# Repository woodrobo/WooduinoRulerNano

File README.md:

# WooduinoRulerNano
WooduinoRulerNanoは定規風Arduino Nano互換機です。  
定規っぽい見た目なだけでなく、電源電流マシマシに設計していて、3.3Vには800mAの3端子レギュレータを採用していて5Vも配線幅的には2Aほど流せます。Vin端子は使ったこと無かったのでつけていないです。  
[BOOTH](https://woodrobo.booth.pm/items/3751720)で販売しています。

# 部品・はんだづけについて
add_info/部品表.csvを見てはんだづけを行ってください。  
(ちなみにCH340GではなくCH340Cを使用すればC3,C4,Y1を省略できます)  
向きを間違えやすい4つの箇所を説明します。  

1.クリスタル(12MHz)  
赤枠が1番ピンなので赤枠同士が合うようにしてください。裏面の方が分かりやすいので裏面も写真にのせています。  

2.CH340G  
〇のマークは1番ピンの意味なので、〇のマークに注目して画像と同様の向きにしてください。  

3.ATMEGA328P  
〇のマークは1番ピンの意味なので、〇のマークに注目して画像と同様の向きにしてください。  

4.LED  
LEDにはアノード・カソードという端子があり極性があります。写真のような向きにしてください。裏面の方が分かりやすいので裏面も写真にのせています。  

# ブートローダ書き込みについて
Arduinoはブートローダと呼ばれるプログラムを書きこむためのプログラムを書きこむことで動作します。公式の説明は[ここ](https://docs.arduino.cc/built-in-examples/arduino-isp/ArduinoISP)。  
ここではArduino Unoを用いてWooduinoRulerNanoに書きこみを行う方法を説明します。(WooduinoRulerNanoはArduino Nano互換機なのでArduino Nanoについて解説されている他のサイトも参考にしてみてください)  

※Arduino Unoの代わりにArduino Nanoを用いてもやり方は同じです。Arduino UnoのところをArduino Nanoに読み替えてください。 それ以外のArduinoから書き込みを行いたい場合は他のサイトを参照してください。 

**テスト環境**  
ArduinoIDE 1.8.13  
Windows 10

**1.まずはArduino Unoにブートローダ書き込み用のプログラムを書きこみます。**

ファイル->スケッチ例->ArduinoISP->ArduinoISPを開きます。  
Arduino Unoに書きこみます。  

**2.Arduino UnoとWooduinoRulerNanoを結線します。**

書き込みには以下の表に示すように6本の配線が必要です。配線時にはどちらも電源供給は行わないでください。RESETの機能に関しては書き込み機と書き込み対象でピンが違うので注意してください。

|  機能  |  書き込み機(Arduino Uno)  |  WooduinoRulerNano
| ---- | ---- |  ----  |
|  MOSI  |  11  |  11  |
|  MISO  |  12  |  12  |
|  SCK  |  13  |  13  |
|  RESET  |  10  |  RESET  |
|  VCC  |  5V  |  5V  |
|  GND  |  GND  |  GND  |

**3.ブートローダを書きこみます。**

書き込み機であるArduino UnoとパソコンをUSBケーブルで接続してください。(WooduinoRulerNanoへはUSBケーブルを**接続しません**)  

ArduinoIDEにて以下のように設定を行います。

- ツール->ボード->Arduino Nano  
- ツール->プロセッサ->ATmega328P  
- 「ツール->シリアルポート」に書き込み装置のArduino Unoのポートを選択
- ツール->書き込み装置->Arduino as ISP

「ツール->ブートローダを書き込む」でSuccessになれば成功です。

**(4.Lチカのプログラムを書きこんでみましょう。)**  

WooduinoRulerNanoとパソコンをUSBケーブルで接続してください。  

ファイル->スケッチ例->01.Basics->Blinkを開きます。  

- ツール->ボード->Arduino Nano  
- ツール->プロセッサ->ATmega328P 
- 「ツール->シリアルポート」にWooduinoRulerNanoのポートを選択
- ツール->書き込み装置->ArduinoISP

書き込んでLチカができたら成功です。  

# トラブルシューティング
Q.WooduinoRulerNanoのUSBまわりがおかしい  
A.WooduinoRulerNanoのUSBシリアル変換にはCH340を使用しているのでUSBドライバがパソコンにインストールされていない可能性があります。CH340のUSBドライバをパソコンに入れてください。

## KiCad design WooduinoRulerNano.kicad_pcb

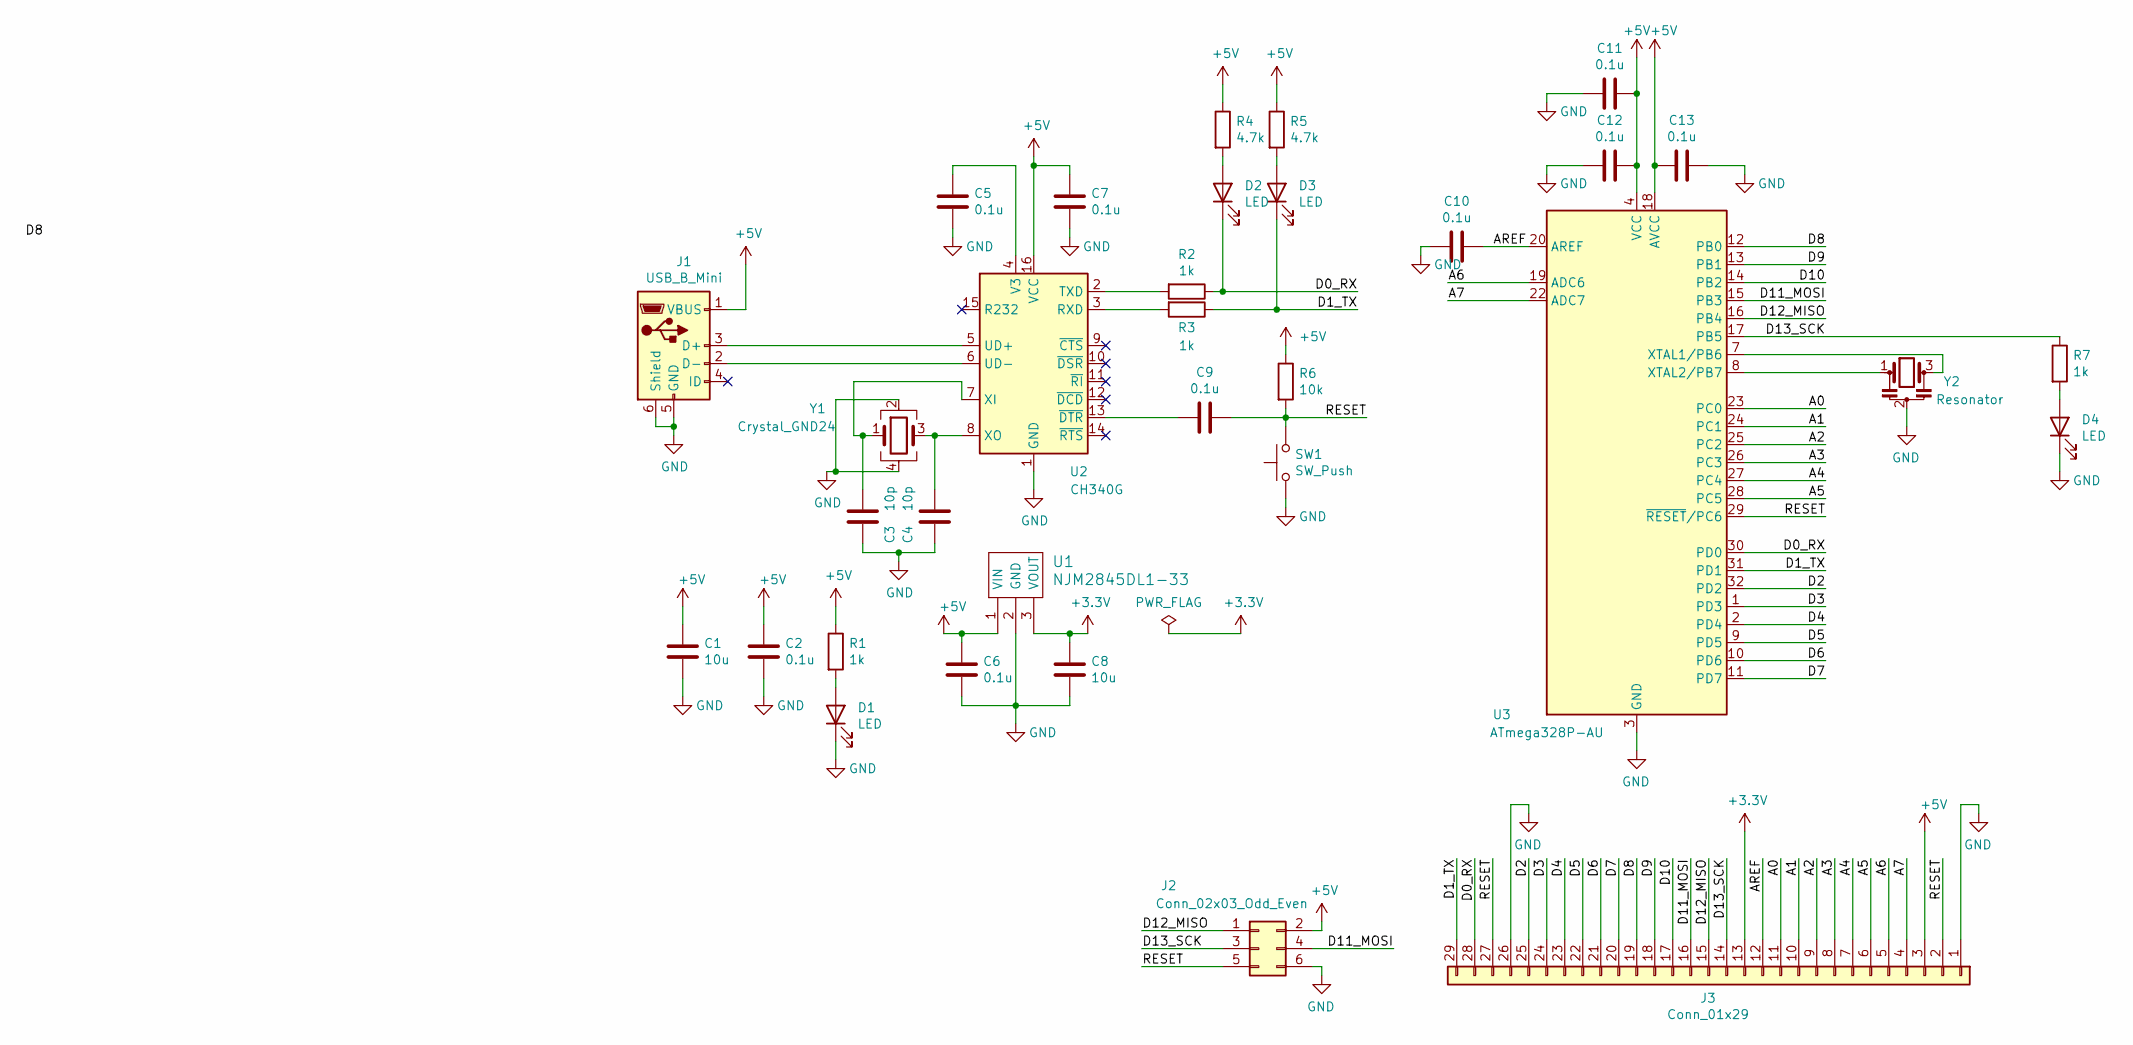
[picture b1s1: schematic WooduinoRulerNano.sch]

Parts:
C1, C8: 10u; C_0603_1608Metric_Pad1.05x0.95mm_HandSolder
C2, C5, C6, C7, C9, C10, C11, C12, C13: 0.1u; C_0603_1608Metric_Pad1.05x0.95mm_HandSolder
C3, C4: 10p; C_0603_1608Metric_Pad1.05x0.95mm_HandSolder
D1, D2, D3, D4: LED; LED_0603_1608Metric_Pad1.05x0.95mm_HandSolder
J1: USB_B_Mini; USB_Mini-B_Wuerth_65100516121_Horizontal
J2: Conn_02x03_Odd_Even; PinHeader_2x03_P2.54mm_Vertical_SMD
J3: Conn_01x29; PinHeader_1x29_P2.54mm_Horizontal_SMD_PSL-410256-29
R1, R2, R3, R7: 1k; R_0603_1608Metric_Pad1.05x0.95mm_HandSolder
R4, R5: 4.7k; R_0603_1608Metric_Pad1.05x0.95mm_HandSolder
R6: 10k; R_0603_1608Metric_Pad1.05x0.95mm_HandSolder
SW1: SW_Push; SW_TVAF06-A020B-R
U1: NJM2845DL1-33; TO-252-2
U2: CH340G; SOIC-16_3.9x9.9mm_P1.27mm
U3: ATmega328P-AU; TQFP-32_7x7mm_P0.8mm
Y1: Crystal_GND24; Crystal_SMD_SeikoEpson_FA238V-4Pin_3.2x2.5mm_HandSoldering
Y2: Resonator; Resonator_SMD_muRata_CSTxExxV-3Pin_3.0x1.1mm_HandSoldering

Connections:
+3V3: C8.2, J3.13, U1.3 (VOUT)
+5V: C1.2, C2.2, C6.2, C7.1, C11.1, C12.1, C13.2, J1.1 (VBUS), J2.2, J3.3, R1.1, R4.1, R5.1, R6.1, U1.1 (VIN), U2.16 (VCC), U3.4 (VCC), U3.6 (VCC), U3.18 (AVCC)
/A0: J3.11, U3.23 (PC0)
/A1: J3.10, U3.24 (PC1)
/A2: J3.9, U3.25 (PC2)
/A3: J3.8, U3.26 (PC3)
/A4: J3.7, U3.27 (PC4)
/A5: J3.6, U3.28 (PC5)
/A6: J3.5, U3.19 (ADC6)
/A7: J3.4, U3.22 (ADC7)
/AREF: C10.1, J3.12, U3.20 (AREF)
/D0_RX: D2.1 (K), J3.28, R2.1, U3.30 (PD0)
/D1_TX: D3.1 (K), J3.29, R3.1, U3.31 (PD1)
/D2: J3.25, U3.32 (PD2)
/D3: J3.24, U3.1 (PD3)
/D4: J3.23, U3.2 (PD4)
/D5: J3.22, U3.9 (PD5)
/D6: J3.21, U3.10 (PD6)
/D7: J3.20, U3.11 (PD7)
/D8: J3.19, U3.12 (PB0)
/D9: J3.18, U3.13 (PB1)
/D10: J3.17, U3.14 (PB2)
/D11_MOSI: J2.4, J3.16, U3.15 (PB3)
/D12_MISO: J2.1, J3.15, U3.16 (PB4)
/D13_SCK: J2.3, J3.14, R7.1, U3.17 (PB5)
/RESET: C9.1, J2.5, J3.2, J3.27, R6.2, SW1.2, U3.29 (~RESET~/PC6)
GND: C1.1, C2.1, C3.2, C4.1, C5.2, C6.1, C7.2, C8.1, C10.2, C11.2, C12.2, C13.1, D1.1 (K), D4.1 (K), J1.5 (GND), J1.6 (Shield), J2.6, J3.1, J3.26, SW1.1, U1.2 (GND), U2.1 (GND), U3.3 (GND), U3.5 (GND), U3.21 (GND), Y1.2, Y1.4, Y2.2
unnamed: C3.1, U2.7 (XI), Y1.1
unnamed: C4.2, U2.8 (XO), Y1.3
unnamed: C5.1, U2.4 (V3)
unnamed: C9.2, U2.13 (~DTR)
unnamed: D1.2 (A), R1.2
unnamed: D2.2 (A), R4.2
unnamed: D3.2 (A), R5.2
unnamed: D4.2 (A), R7.2
unnamed: J1.2 (D-), U2.6 (UD-)
unnamed: J1.3 (D+), U2.5 (UD+)
unnamed: R2.2, U2.2 (TXD)
unnamed: R3.2, U2.3 (RXD)
unnamed: U3.7 (XTAL1/PB6), Y2.3
unnamed: U3.8 (XTAL2/PB7), Y2.1

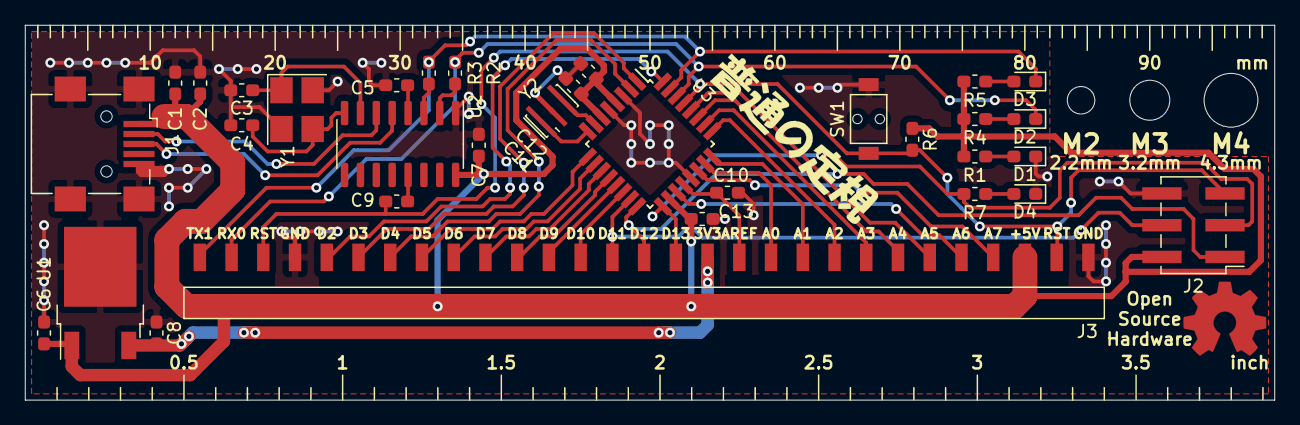
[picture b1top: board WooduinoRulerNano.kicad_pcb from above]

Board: 2 copper layers, 100.0 x 30.0 mm, 33 parts (0 on the bottom side), 41 nets.

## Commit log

2022-11-12 設計でけた
2022-11-13 部品表と部品個数表を追加
2022-12-22 readme途中まで書いた
2022-12-22 readmeの画像リンクを直した
2022-12-22 readmeの画像リンクをさらに直した
2022-12-22 readmeの改行ミスを直した
2022-12-22 readmeにBoothのURLを追加
2023-01-07 ブートローダの書き込みを追加
